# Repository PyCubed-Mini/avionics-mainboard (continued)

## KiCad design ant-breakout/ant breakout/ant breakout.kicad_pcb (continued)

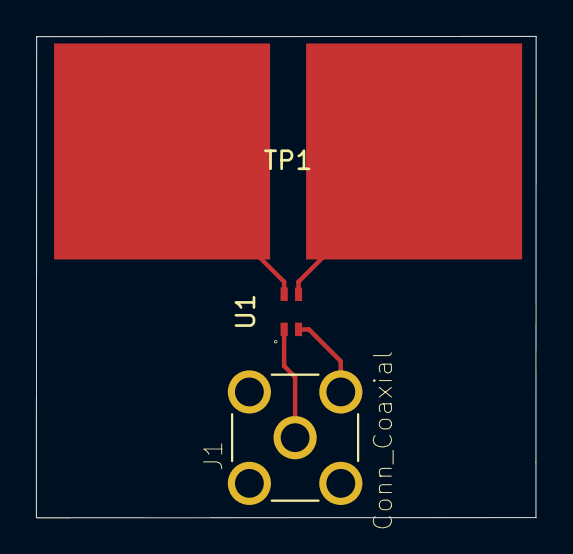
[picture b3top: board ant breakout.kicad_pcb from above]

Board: 2 copper layers, 27.8 x 26.7 mm, 3 parts (0 on the bottom side), 4 nets.

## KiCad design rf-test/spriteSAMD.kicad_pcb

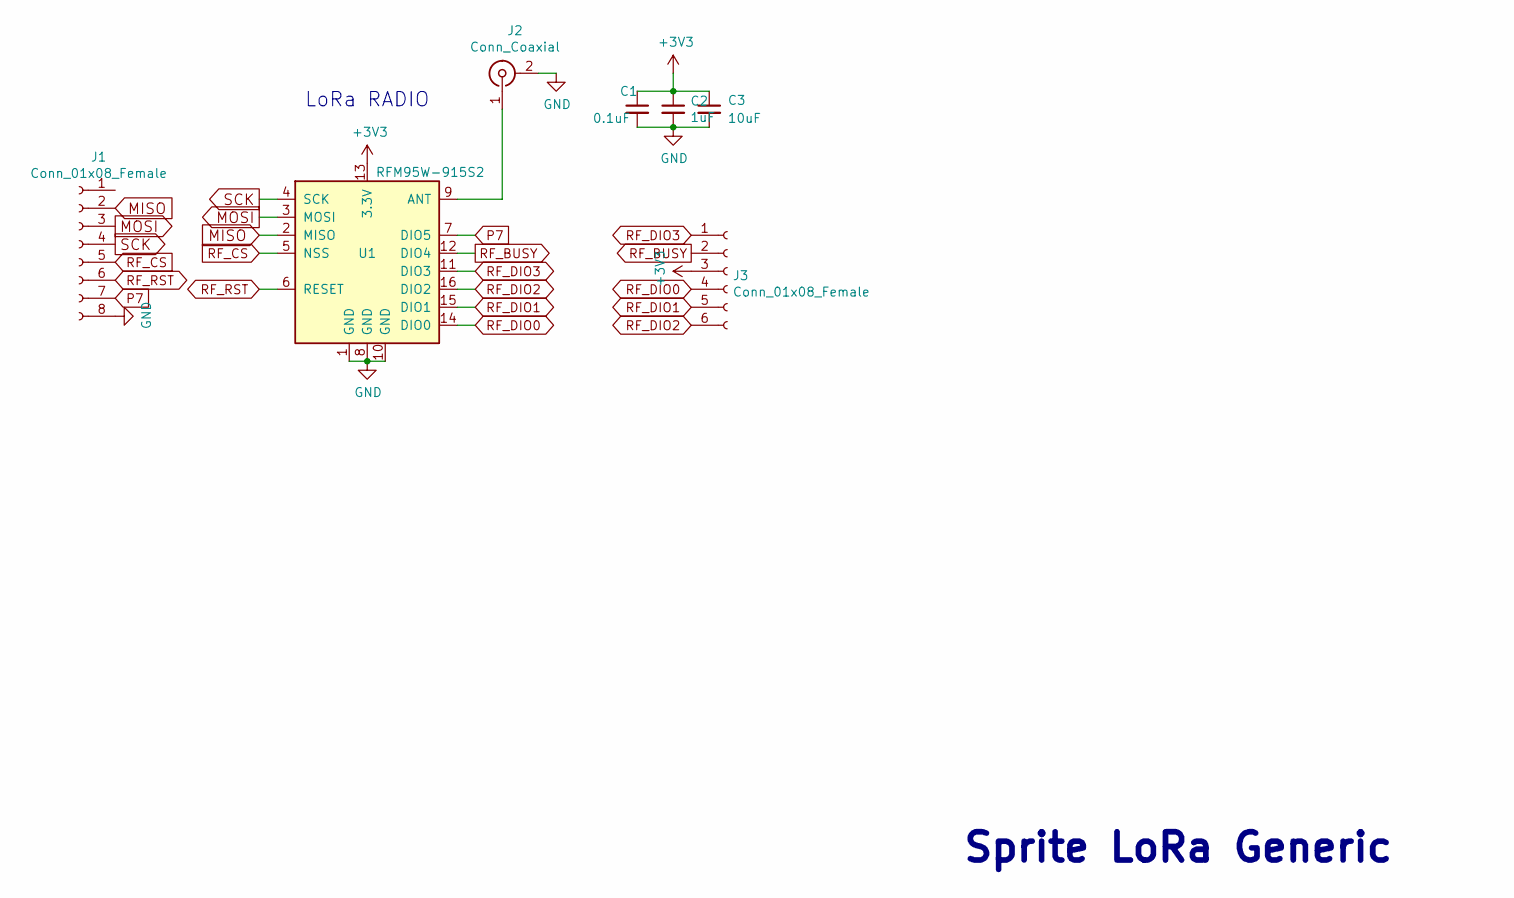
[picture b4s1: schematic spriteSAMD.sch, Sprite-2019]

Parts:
C1: 0.1uF; C_0402_1005Metric
C2: 1uF; C_0402_1005Metric
C3: 10uF; C_0402_1005Metric
J1: Conn_01x08_Female; PinHeader_1x08_P2.54mm_Vertical
J2: Conn_Coaxial; SMA_Samtec_SMA-J-P-H-ST-EM1_EdgeMount
J3: Conn_01x08_Female; PinHeader_1x06_P2.54mm_Vertical
U1: RFM95W-915S2; HOPERF_RFM9XW_SMD

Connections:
+3V3: C1.1, C2.1, C3.1, J3.3, U1.13 (3.3V)
GND: C1.2, C2.2, C3.2, J1.8, J2.2 (Ext), U1.1 (GND), U1.8 (GND), U1.10 (GND)
MISO: J1.2, U1.2 (MISO)
MOSI: J1.3, U1.3 (MOSI)
unnamed: J2.1 (In), U1.9 (ANT)
P7: J1.7, U1.7 (DIO5)
RF_BUSY: J3.2, U1.12 (DIO4)
RF_CS: J1.5, U1.5 (NSS)
RF_DIO0: J3.4, U1.14 (DIO0)
RF_DIO1: J3.5, U1.15 (DIO1)
RF_DIO2: J3.6, U1.16 (DIO2)
RF_DIO3: J3.1, U1.11 (DIO3)
RF_RST: J1.6, U1.6 (RESET)
SCK: J1.4, U1.4 (SCK)

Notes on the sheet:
LoRa RADIO
Sprite LoRa Generic

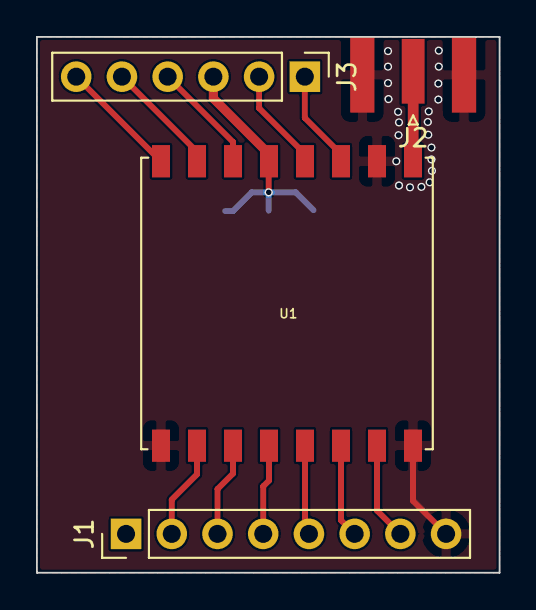
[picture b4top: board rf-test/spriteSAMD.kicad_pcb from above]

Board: 2 copper layers, 25.7 x 29.8 mm, 7 parts (0 on the bottom side), 14 nets.

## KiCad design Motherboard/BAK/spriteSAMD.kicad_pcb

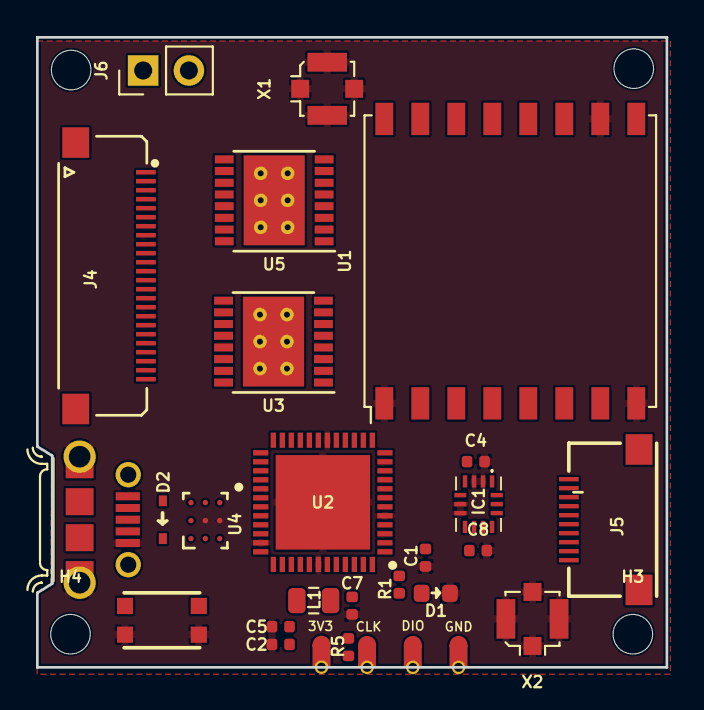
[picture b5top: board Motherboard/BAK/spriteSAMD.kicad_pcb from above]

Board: 4 copper layers, 35.0 x 35.0 mm, 39 parts (0 on the bottom side), 23 nets, no tracks yet.

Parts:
C1, C4, C8: 0.1uF; C_0402_1005Metric
C2, C7: 10uF; C_0402_1005Metric
C3, C5, C6: 1uF; C_0402_1005Metric
D1: GREEN; LED_0603_1608Metric
D2: RB550V; D_SOD-323
H1, H2, H3, H4: MountingHole; MountingHole_2.2mm_M2
IC1: BMX160
J1, J28, J29, J30: Conn_01x01; castellated_small_1side
J2: 10118194-0001LF
J3: Micro_SD_Card; 503182-1853_MOLEX-MicroSD
J4: xf2m-2415-1a; XF2M-2415-1A
J5: XF2M-1015-1A
J6: Conn_01x02; PinHeader_1x02_P2.54mm_Vertical
L1: 10uH; L_0805_2012Metric
R1: 330; R_0402_1005Metric
R2, R3, R5: 10K; R_0402_1005Metric
SW1: KMR231NG LFS; BTN_KMR2_4.6X2.8
U1, U8: RFM95W-915S2; HOPERF_RFM9XW_SMD
U2: ATSAMD51G_TQFN48; QFN50P700X700X90-49N-D
U3, U5: DRV8833PWP; HTSSOP-16-1EP_4.4x5mm_P0.65mm_EP3.4x5mm_Mask2.46x2.31mm_The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
U4: TPS82740BSIPR; TPS82740ASIPR
U6: MAX708RESA-T; SO-8_3.9x4.9mm_P1.27mm
X1, X2: ANTENNA_U.FL; U.FL_Molex_MCRF_73412-0110_Vertical

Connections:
+3V3: C1.1, C3.1, C4.1, C7.1, C8.1, IC1.5, IC1.8, J3.4, J29.1, R2.2, R5.1, U1.13, U2.4, U2.6, U2.17, U2.36, U2.44, U4.C1, U6.2, U8.13
/LED1: R1.2, U2.48
/SWCLK: J28.1, R5.2, U2.45
/SWDIO: J1.1, U2.46
/USB+: J2.3, U2.34
/USB-: J2.2, U2.33
GND: C1.2, C2.2, C3.2, C4.2, C5.2, C6.1, C7.2, C8.2, D1.2, IC1.2, IC1.3, IC1.6, IC1.7, J2.5, J2.8, J2.9, J3.6, J30.1, SW1.B, SW1.B', U1.1, U1.8, U1.10, U2.5, U2.18, U2.35, U2.42, U2.49, U4.B2, U4.C2, U6.3, U6.4, U8.1, U8.8, U8.10, X1.1, X1.2, X2.1, X2.2
MISO: IC1.1, J3.7, U1.2, U2.15, U8.2
MOSI: IC1.14, J3.3, U1.3, U2.13, U8.3
unnamed: C2.1, C5.1, L1.2, U2.41
unnamed: D1.1, R1.1
unnamed: D2.1, U4.A1, U4.A2, U4.A3, U4.B3, U4.C3
unnamed: L1.1, U2.43
unnamed: R3.2, U6.7, U6.8
RF_BUSY: U2.1, U8.12
RF_DIO0: U2.47, U8.14
RF_DIO1: U2.39, U8.15
RF_DIO2: U2.38, U8.16
RF_DIO3: U2.2, U8.11
RF_RST: U2.21, U8.6
SCK: IC1.13, J3.5, U1.4, U2.14, U8.4
VUSB: D2.2, J2.1
~RESET: C6.2, R2.1, R3.1, SW1.A, SW1.A', U2.40

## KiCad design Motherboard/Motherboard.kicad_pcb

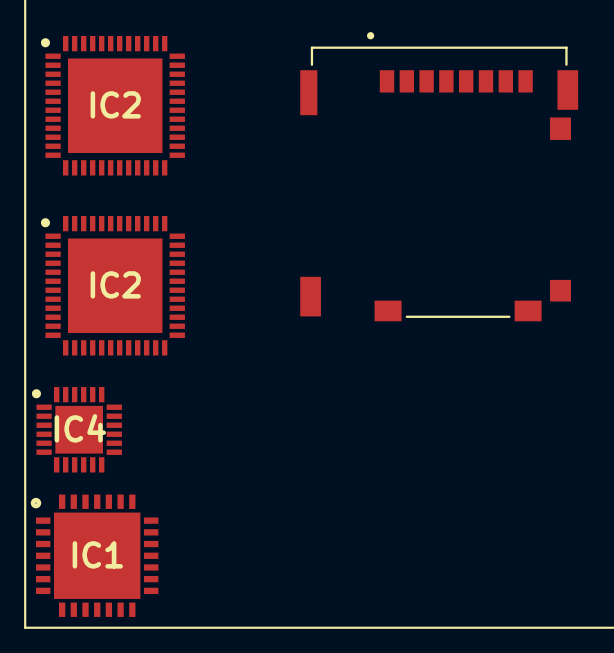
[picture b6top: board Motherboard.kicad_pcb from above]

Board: 2 copper layers, 5 parts (0 on the bottom side), 50 nets, no tracks yet.

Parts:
IC1: SX1278IMLTRT; QFN65P600X600X100-29N-D
IC2, IC2#2: ATSAMD51G18A-MU; QFN50P700X700X90-49N-D
IC4: SX1280IMLTRT; QFN50P400X400X80-25N-D
J1: 503182-1852; MOLEX_503182-1852

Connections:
unnamed: IC2.1, IC2#2.1
unnamed: IC2.2, IC2#2.2
unnamed: IC2.3, IC2#2.3
unnamed: IC2.4, IC2#2.4
unnamed: IC2.5, IC2#2.5
unnamed: IC2.6, IC2#2.6
unnamed: IC2.7, IC2#2.7
unnamed: IC2.8, IC2#2.8
unnamed: IC2.9, IC2#2.9
unnamed: IC2.10, IC2#2.10
unnamed: IC2.11, IC2#2.11
unnamed: IC2.12, IC2#2.12
unnamed: IC2.13, IC2#2.13
unnamed: IC2.14, IC2#2.14
unnamed: IC2.15, IC2#2.15
unnamed: IC2.16, IC2#2.16
unnamed: IC2.17, IC2#2.17
unnamed: IC2.18, IC2#2.18
unnamed: IC2.19, IC2#2.19
unnamed: IC2.20, IC2#2.20
unnamed: IC2.21, IC2#2.21
unnamed: IC2.22, IC2#2.22
unnamed: IC2.23, IC2#2.23
unnamed: IC2.24, IC2#2.24
unnamed: IC2.25, IC2#2.25
unnamed: IC2.26, IC2#2.26
unnamed: IC2.27, IC2#2.27
unnamed: IC2.28, IC2#2.28
unnamed: IC2.29, IC2#2.29
unnamed: IC2.30, IC2#2.30
unnamed: IC2.31, IC2#2.31
unnamed: IC2.32, IC2#2.32
unnamed: IC2.33, IC2#2.33
unnamed: IC2.34, IC2#2.34
unnamed: IC2.35, IC2#2.35
unnamed: IC2.36, IC2#2.36
unnamed: IC2.37, IC2#2.37
unnamed: IC2.38, IC2#2.38
unnamed: IC2.39, IC2#2.39
unnamed: IC2.40, IC2#2.40
unnamed: IC2.41, IC2#2.41
unnamed: IC2.42, IC2#2.42
unnamed: IC2.43, IC2#2.43
unnamed: IC2.44, IC2#2.44
unnamed: IC2.45, IC2#2.45
unnamed: IC2.46, IC2#2.46
unnamed: IC2.47, IC2#2.47
unnamed: IC2.48, IC2#2.48
unnamed: IC2.49, IC2#2.49
unnamed: J1.P1, J1.P2, J1.P3, J1.P4, J1.P5

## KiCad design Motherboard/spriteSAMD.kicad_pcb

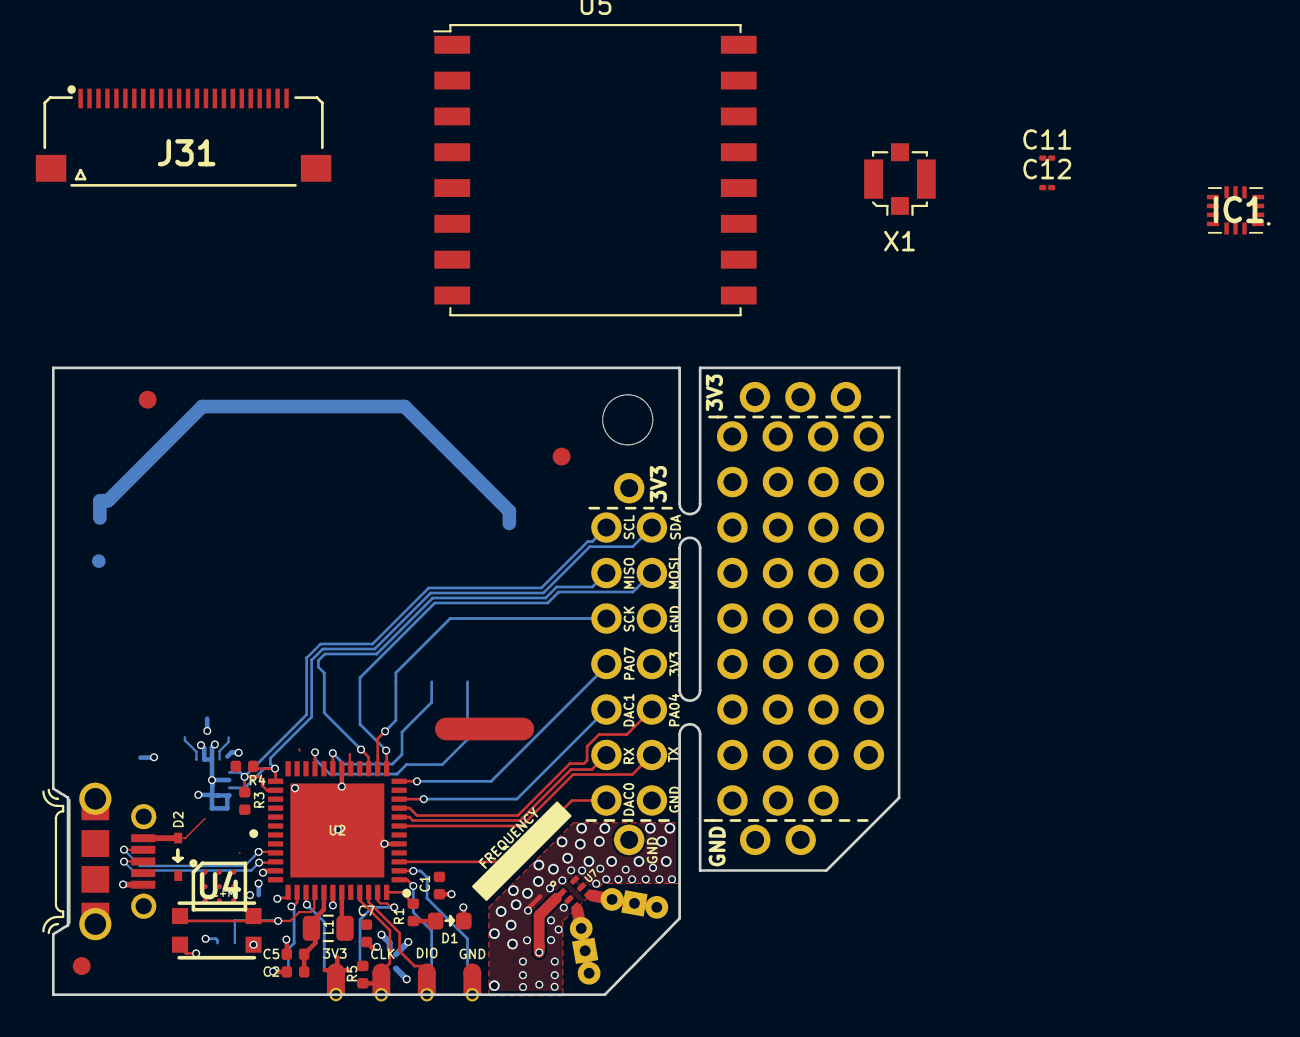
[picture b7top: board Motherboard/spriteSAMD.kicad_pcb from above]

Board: 4 copper layers, 47.2 x 35.0 mm, 64 parts (0 on the bottom side), 35 nets.

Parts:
@HOLE0: (no value)
ANT1, ANT2: ANTENNA
C1, C8, C10: 0.1uF; C_0402_1005Metric
C2, C4, C7: 10uF; C_0402_1005Metric
C3, C5, C6: 1uF; C_0402_1005Metric
C9: 10nF; C_0402_1005Metric
C11, C12: 100 nF; C_01005_0402Metric
D1: GREEN; LED_0603_1608Metric
D2: RB550V; D_SOD-323
IC1: BMX160
J1, J28, J29, J30: Conn_01x01; castellated_small_1side
J2: 10118194-0001LF
J3, J4, J5, J6, J7, J8, J9, J10, J11, J12: Conn_01x01; PinHeader_CUSTOM2
J13, J14, J15, J16, J17, J18, J19, J20: Conn_01x04; PinHeader_CUSTOM
J21, J22, J23, J24, J25, J26, J27: Conn_01x02; PinHeader_CUSTOM3
J31: xf2m-2415-1a; XF2M-2415-1A
L1: 10uH; L_0805_2012Metric
R1: 330; R_0402_1005Metric
R2, R3, R4, R5: 10K; R_0402_1005Metric
SW1: KMR231NG LFS; BTN_KMR2_4.6X2.8
U1: LSM9DS1; LGA24-8X4
U2: ATSAMD51G_TQFN48; QFN50P700X700X90-49N-D
U3: BAT-HLD-001
U4: TPS82740ASIP-TPS82740; BGA9C80P3X3_290X230X110
U5, U8: RFM95W-915S2; HOPERF_RFM9XW_SMD
U7: HHM17139B2; balun0603
X1: ANTENNA_U.FL; U.FL_Molex_MCRF_73412-0110_Vertical

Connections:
+3V3: C1.1, C3.1, C4.2, C7.1, C8.2, C11.1, C12.1, IC1.5, IC1.8, J6.1, J7.1, J8.1, J12.1, J25.2, J29.1, R2.2, R3.1, R4.1, R5.1, U1.1, U1.3, U1.5, U1.6, U1.7, U1.8, U1.22, U1.23, U2.4, U2.6, U2.17, U2.36, U2.44, U4.C1, U5.13, U8.13
/LED1: R1.2, U2.48
/SWCLK: J28.1, R5.2, U2.45
/SWDIO: J1.1, U2.46
/USB+: J2.3, U2.34
/USB-: J2.2, U2.33
DAC0: J27.1, U2.3
DAC1: J24.1, U2.10
GND: C1.2, C2.2, C3.2, C4.1, C5.2, C6.1, C7.2, C8.1, C9.1, C10.1, C11.2, C12.2, D1.2, IC1.2, IC1.3, IC1.6, IC1.7, J2.5, J2.8, J2.9, J9.1, J10.1, J11.1, J22.2, J27.2, J30.1, SW1.B, SW1.B', U1.14, U1.15, U1.16, U1.17, U1.18, U1.19, U1.20, U2.5, U2.18, U2.35, U2.42, U2.49, U3.2, U4.B2, U4.C2, U5.1, U5.8, U5.10, U7.2, U7.5, U7.6, U8.1, U8.8, U8.10, X1.1, X1.2
MISO: J23.1, U2.15, U5.2, U8.2
MOSI: J23.2, U2.13, U5.3, U8.3
unnamed: ANT1.IN1, ANT1.IN2, ANT1.IN3, U7.3
unnamed: ANT2.IN1, ANT2.IN2, ANT2.IN3, U7.4
unnamed: C2.1, C5.1, L1.2, U2.41
unnamed: C6.2, R2.1, SW1.A, SW1.A', U2.40
unnamed: C9.2, U1.21
unnamed: C10.2, U1.24
unnamed: D1.1, R1.1
unnamed: D2.1, U3.1, U3.3, U4.C3
unnamed: L1.1, U2.43
PA04: J24.2, U2.9
PA07: J25.1, U2.12
RF_BUSY: U2.1, U5.12, U8.12
RF_CS: U2.19, U5.5, U8.5
RF_DIO0: U2.47, U5.14, U8.14
RF_DIO1: U2.39, U5.15, U8.15
RF_DIO2: U2.38, U5.16, U8.16
RF_DIO3: U2.2, U5.11, U8.11
RF_RST: U2.21, U5.6, U8.6
RX: J21.1, U2.8
SCK: J22.1, U2.14, U5.4, U8.4
SCL: IC1.13, J26.1, R3.2, U1.2, U2.26
SDA: IC1.14, J26.2, R4.2, U1.4, U2.25
TX: J21.2, U2.7
VUSB: D2.2, J2.1, U4.A1, U4.A2, U4.A3, U4.B3

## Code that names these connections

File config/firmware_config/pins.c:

#include "shared-bindings/board/__init__.h"
#include "supervisor/board.h"

STATIC const mp_rom_map_elem_t board_global_dict_table[] = {
    CIRCUITPYTHON_BOARD_DICT_STANDARD_ITEMS

    { MP_ROM_QSTR(MP_QSTR_SCK),      MP_ROM_PTR(&pin_PA13) },
    { MP_ROM_QSTR(MP_QSTR_MOSI),     MP_ROM_PTR(&pin_PA12) },
    { MP_ROM_QSTR(MP_QSTR_MISO),     MP_ROM_PTR(&pin_PA14) },

    { MP_ROM_QSTR(MP_QSTR_SDA1),     MP_ROM_PTR(&pin_PA22) },
    { MP_ROM_QSTR(MP_QSTR_SCL1),     MP_ROM_PTR(&pin_PA23) },
    { MP_ROM_QSTR(MP_QSTR_SDA2),     MP_ROM_PTR(&pin_PA16) },
    { MP_ROM_QSTR(MP_QSTR_SCL2),     MP_ROM_PTR(&pin_PA17) },
    { MP_ROM_QSTR(MP_QSTR_SDA3),     MP_ROM_PTR(&pin_PB12) },
    { MP_ROM_QSTR(MP_QSTR_SCL3),     MP_ROM_PTR(&pin_PB13) },

    { MP_ROM_QSTR(MP_QSTR_TX0),      MP_ROM_PTR(&pin_PA04) },
    { MP_ROM_QSTR(MP_QSTR_RX0),      MP_ROM_PTR(&pin_PA05) },
    { MP_ROM_QSTR(MP_QSTR_TX1),      MP_ROM_PTR(&pin_PB16) },
    { MP_ROM_QSTR(MP_QSTR_RX1),      MP_ROM_PTR(&pin_PB17) },

    { MP_ROM_QSTR(MP_QSTR_RF_IO0),   MP_ROM_PTR(&pin_PA27) },
    { MP_ROM_QSTR(MP_QSTR_RF_IO1),   MP_ROM_PTR(&pin_PB23) },
    { MP_ROM_QSTR(MP_QSTR_RF_RST),   MP_ROM_PTR(&pin_PA20) },
    { MP_ROM_QSTR(MP_QSTR_RF_CS),    MP_ROM_PTR(&pin_PB31) },

    { MP_ROM_QSTR(MP_QSTR_BURN1),    MP_ROM_PTR(&pin_PA19) },
    { MP_ROM_QSTR(MP_QSTR_BURN2),    MP_ROM_PTR(&pin_PA18) },
    { MP_ROM_QSTR(MP_QSTR_WDT_WDI),  MP_ROM_PTR(&pin_PB30) },
    { MP_ROM_QSTR(MP_QSTR_WDT_EN),   MP_ROM_PTR(&pin_PB22) },
    { MP_ROM_QSTR(MP_QSTR_NEOPIXEL), MP_ROM_PTR(&pin_PA21) },
    { MP_ROM_QSTR(MP_QSTR_BATTERY),  MP_ROM_PTR(&pin_PA06) },

    { MP_ROM_QSTR(MP_QSTR_PAYLOAD_CS),  MP_ROM_PTR(&pin_PB08) },
    { MP_ROM_QSTR(MP_QSTR_PAYLOAD_EN),  MP_ROM_PTR(&pin_PB09) },
    { MP_ROM_QSTR(MP_QSTR_M_FAULT),     MP_ROM_PTR(&pin_PB14) },
    { MP_ROM_QSTR(MP_QSTR_SD_CS),       MP_ROM_PTR(&pin_PB15) },

    { MP_ROM_QSTR(MP_QSTR_I2C),      MP_ROM_PTR(&board_i2c_obj)  },
    { MP_ROM_QSTR(MP_QSTR_SPI),      MP_ROM_PTR(&board_spi_obj)  },
    { MP_ROM_QSTR(MP_QSTR_UART),     MP_ROM_PTR(&board_uart_obj) },
};
MP_DEFINE_CONST_DICT(board_module_globals, board_global_dict_table);

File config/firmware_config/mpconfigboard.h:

#define MICROPY_HW_BOARD_NAME "PyCubedMini"
#define MICROPY_HW_MCU_NAME "samd51j20"
#define CIRCUITPY_MCU_FAMILY samd51

#define MICROPY_HW_NEOPIXEL   (&pin_PA21)

#define MICROPY_PORT_A        (PORT_PA08 | PORT_PA09 | PORT_PA10 | PORT_PA11)
#define MICROPY_PORT_B        (PORT_PB10 | PORT_PB11)
#define MICROPY_PORT_C        (0)
#define MICROPY_PORT_D        (0)

#define SPI_FLASH_WP_PIN            &pin_PA10
#define SPI_FLASH_HOLD_PIN          &pin_PA11

// External flash MR2xH40 MRAM
#define EXTERNAL_FLASH_QSPI_SINGLE
#define EXTERNAL_FLASH_NO_JEDEC

#define AUTORESET_DELAY_MS 500

#define BOARD_HAS_CRYSTAL 1

#define DEFAULT_I2C_BUS_SCL  (&pin_PA23)
#define DEFAULT_I2C_BUS_SDA  (&pin_PA22)

#define DEFAULT_SPI_BUS_SCK  (&pin_PA13)
#define DEFAULT_SPI_BUS_MOSI (&pin_PA12)
#define DEFAULT_SPI_BUS_MISO (&pin_PA14)

#define DEFAULT_UART_BUS_RX  (&pin_PA05)
#define DEFAULT_UART_BUS_TX  (&pin_PA04)

#define IGNORE_PIN_PA24     1
#define IGNORE_PIN_PA25     1

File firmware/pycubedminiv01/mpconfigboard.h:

#define MICROPY_HW_BOARD_NAME "PyCubedMini"
#define MICROPY_HW_MCU_NAME "samd51G19"
#define CIRCUITPY_MCU_FAMILY samd51

#define MICROPY_HW_NEOPIXEL   (&pin_PB22)

#define MICROPY_PORT_A        (PORT_PA24 | PORT_PA25)
#define MICROPY_PORT_B        (0)
#define MICROPY_PORT_C        (0)
#define MICROPY_PORT_D 		  (0)

#define CALIBRATE_CRYSTALLESS 1

#define CIRCUITPY_INTERNAL_NVM_SIZE 0

#define BOARD_FLASH_SIZE (FLASH_SIZE - 0x4000 - 0x010000)

#define DEFAULT_I2C_BUS_SCL  (&pin_PA16)
#define DEFAULT_I2C_BUS_SDA  (&pin_PA17)

#define DEFAULT_SPI_BUS_SCK  (&pin_PA09)
#define DEFAULT_SPI_BUS_MOSI (&pin_PA08)
#define DEFAULT_SPI_BUS_MISO (&pin_PA10)

#define IGNORE_PIN_PA24     1
#define IGNORE_PIN_PA25     1

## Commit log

2019-10-03 adding sprite reference design
2019-10-14 Create components
    Documenting component design decisions
2019-10-14 First take at schematic and PCB Design
    Includes SAMD51 MCU, Semtech 1280 UHF module, Semtech 1278 LoRa Module, and a micro SD card module
2019-10-16 Motherboard
    Updated with SAMD51, LoRA and UHF modules, IMU, and MicroSD card module
2019-10-16 cleaning up reference design
2019-10-21 Updated Avionics Motherboard Based on Sprite Design
    Changes from Sprite design:
    - Added two radio modules and corresponding antennae
    - Disconnected regulator from solar cells / battery power
    - Added BMX 160 IMU (original Sprite IMU left on board for discussion)
    - Added flat flex connector (24 pins)
2019-10-22 Add files via upload
    commiting changes again
2019-10-22 adding second I2C bus and fixing SPI pins
2019-10-22 adding pull-up resistors to I2C
2019-10-22 removing confusing files
2019-10-22 experiment for schematic "snapshot"
2019-10-22 adding quick schematic snapshot
2019-10-22 quick step export for CAD
2019-10-23 updated PCB layout
2019-10-23 updated H-bridge nets on schematic
2019-10-23 updated H-bridge footprints with footprints from component search engine
2019-10-23 updated top layer PCB layout
2019-10-23 updated placement of H-bridges, flat flex connector, and additional wirings
2019-10-23 updated wiring on top layer, added CS_IMU net
2019-10-23 updating board outline to tentative design per @ellised discussion
2019-10-23 quick STEP file for mechanical team
2019-10-23 updated wiring on top layer, added CS_IMU connections
2019-10-23 updated camera connector and connected to MCU and flat flex connector
2019-10-23 added vias to flat flex connector, added traces to comm protocols off of MCU
2019-10-23 added WDT_WDI net to MCU, connected C2, C5, and L1 to MCU
2019-10-23 added traces for J29, J28, J30
2019-10-23 deleted accidental bottom traces on bottom of board
2019-10-23 updated position of UHF on bottom of board to not overlap MCU
2019-10-23 added watchdog timer footprint to PCB layout
2019-10-23 added comm vias and traces to LoRa radio module on top layer
2019-10-23 added SCL2 and SDA2 traces between MCU and flat flex connector
2019-10-23 updated location of USB and watchdog timer on top layer, connected watchdog timer to R3 and reset nest on MCU
2019-10-23 updated board outline to match re-location of USB
2019-10-23 updated H-bridge positions on bottom layer
2019-10-23 updated H-bridge positions traces with capacitors on bottom layer
2019-10-23 updated traces for UHF and SD card on bottom layer
2019-10-23 updated bottom layer traces
2019-10-24 put top layer back in after accidentally deleting it....
2019-10-24 updated H-bridge voltage nests on schematic, updated traces on PCB for H-bridges to flat flex connector and for watchdog timer
2019-10-24 finished final touches for motherboard first draft
2019-10-24 placement rework with 2019-10-23 mechanical updates
2019-10-24 mainboard files
2019-10-24 added routing for flex connectors to hbridge
2019-10-25 very minor cleanup
2019-10-26 fab files for mainboard
2019-10-26 Added RF test board
2019-10-26 fab output for JLCPCB
2019-10-26 interactive BOM
2019-10-30 Add files via upload
    imported .dxf board outline from mechanical
2019-10-31 modified board outline based on update from mechanical, including USB slot
2019-11-12 Fixed Mistake in RF Test Board
2019-11-13 created folder to dump kicad antennae breakout
2019-11-13 deleted ant-breakout
2019-11-13 created folder to dump ant-breakout
2019-11-13 added antennae breakout board files
2019-11-13 deleting placeholder file
2019-11-13 Updated files
2019-11-14 updated footprint
2019-11-15 Dxf file of the internal board cutout.
2019-11-17 Create Hbridge Test Code
2019-11-19 associated pin names with variables
2019-11-19 updated edge cuts to match updated mechanical .dxf file (to allow flat flex connectors to travel around board edge)
2019-11-19 updated bottom layer edge mapping to edge cuts, deleted most vias/traces and started reworking component placement.
2019-11-20 Updated component placement on top and bottom faces (no traces)
2019-11-20 started routing with new layout
2019-11-20 updated layout with new camera connector placement, more traces, removed mounting holes
2019-11-20 updated footprints for U.FL connectors, more traces added
2019-11-20 updated KiCAD libraries with new footprints from component search engine
2019-11-20 updated camera placement to avoid vertical pulling
2019-11-20 updated traces
2019-11-21 adjusted ordering in flat flex connector to avoid ratsnest crossings for Hbridges, added camera traces
2019-11-21 updated pycubed board edge cuts, updated top layer copper edges, shifted USB card and flat flex connector (still need to shift camera connector)
2019-11-27 create second main file
    created another main file for playing with hbridge
2019-12-13 Added link to block diagram file for editing
2019-12-13 Updated draw.io link
2020-01-01 adding v01 + repo overhaul
2020-01-30 adding default libraries, examples, and PIN-NAMES.txt
2020-01-30 adding readme...?
2020-01-31 fixed CP build files to accmodate recent .ld implimentation changes.
2020-02-18 added git ignore for kicad backup files
2020-02-18 Updated magnetorquer driver and fixed some PCB DRC issues
2020-02-20 updated 3d footprint paths and generated new step file
2020-03-01 added fiducials, regenerated 3d model and gerbers
2020-08-11 schematic work
2020-08-11 finished schematic changes
2020-08-20 updated footprints
2020-08-21 power coil drivers directly from battery
2020-08-21 cleaned off layout
2020-08-24 beginning layout
2020-08-24 some routing
2020-08-25 lots of routing
2020-08-25 layout minus dosimeter
2020-08-25 initial layout done
2020-08-25 RGB LED
2020-08-26 changed LDO and added RBF header
2020-08-26 BATT_P cleanup. starting dosimeter tweaks
2020-08-26 fit-checked with CAD
2020-08-26 removed dosimeter & roughed in new RBF header
2020-08-26 roughed-in SD card
2020-08-26 routed
2020-08-26 added xtal
2020-08-26 silkscreen placed
2020-08-26 updating CAD models
2020-08-26 pretty BOM and schematic pdf
2020-08-26 ran DRC & added pullups
2020-08-26 manufacturing files + JLCPCB order placed
2020-08-30 fixed WDT part number
2020-09-04 bootloader for new mainboard
2020-09-04 firmware for new mainboard
2020-09-15 mram firmware
2022-02-16 built firmware for CP7.2 alpha
2022-02-16 adding firmware readme
2022-02-16 forgot to commit the actual firmware.uf2
2022-02-19 Cleaned schematic, and moved components
2022-02-23 Made suggested changes
2022-02-23 Updated BOM
2022-02-24 Curved radio trace
2022-02-27 Moved Rf Antenna. Change J7 to 1x5 Header
2022-02-27 Expanded inner ground trace
2022-02-28 stop tracking fp-info-cache
2022-03-02 Moved RBF Header to under micro USB port
2022-03-04 Updated 3D Models
2022-03-04 Update Kicad-libs
2022-03-04 Assign Radio 3D model
2022-03-05 Added Step file
2022-03-12 Replaced Flat flex connector with one in stock + updated step model
2022-03-13 Changed Flex connector to one from the same family as the one on the solar panels
2022-03-13 Removed redundant library
2022-03-14 Pulled latest lib changes
2022-03-16 Exported Gerber Files
2022-05-04 stack outline
2022-05-09 new mainboard outline
2022-05-09 Stack Schematic changes
2022-05-14 Finished v03 routing
2022-05-14 Grounded Mounting Holes
2022-05-16 updated board outline
2022-05-16 Suggested changes
2022-05-17 Exported Step Model
2022-05-24 Moved back mounting holes to 3.5mm from board edges
2022-06-02 added dxf file of mainboard
2022-06-02 Some changes plus new step file
2022-06-03 Firmware updates for ATSAMD51J19A
2022-06-08 Updated stack connectors and added SPDT switch
2022-06-08 added pulldown and 0 ohm resistor to VBUS. Renamed VBUS to VUSB
2022-06-09 Added Logo, version number, and date
2022-06-10 Exported Gerbers
2022-06-24 Updated Mainboard-Solar Panels X/Z Connectors
2022-06-27 Moved Batteryboard connector to avoid solder interference
2022-06-27 updated 3D model
2022-06-29 Recheck board and re-export model
2022-07-06 Export New Gerbers
2022-08-11 burnwire pin updates
2022-08-21 v05 Updates
2022-08-31 Rev A/01 Updates
2022-08-31 Updated Revision Number to B/03
2022-09-02 Repositioned Solar Panel Connectors
2022-09-02 Added RF cable routing cutout
2022-09-06 Made BATT_P a Copper Fill
2022-09-22 stuff
2022-09-22 Changes stash
2022-09-26 Lots of updates
2022-09-27 More updates
2022-09-28 Finished routing
2022-09-29 Some fixes
2022-09-29 Changed stack connectors to SMD ones
2022-10-09 Finished B2/01 Updates
2022-10-09 Added Pullup to SD CS
2022-11-09 right-angle reset button + export STEP / BOM
2022-11-11 DFM Updates
2022-11-11 Export Gerbers
2023-02-18 Cleanup
2023-02-18 Stash before major changes
2023-02-18 Finished routing Rev B3/01
2023-02-18 Updated Schematic to reflect RTC on I2C 1
2023-02-19 Minor updates
2023-02-25 Moved Neopixel to be visible through X board hole
2023-02-26 Removed gerbers from repo
2023-04-26 Rev B3/02 Updates
2023-04-26 Leftover updates
2023-06-18 Re-wired IMU to use UART
2023-06-19 Moved Rev label to be visible post-assembly
2023-06-19 Pull kicad-libs
2023-06-20 PCB cleanup
2023-12-18 Rev B3/04 Updates
2023-12-27 Stash C1 Updates
2024-01-18 Added Alternate I2C routing for IMU
2024-04-29 Updated config folder for latest hardware rev
2024-04-29 Auto stash before merge of "C1/01-Updates" and "origin/C1/01-Updates"
2024-04-29 Actually update firmware config files
2024-04-29 Actually update firmware.uf2 file
